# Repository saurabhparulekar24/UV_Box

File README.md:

# UV_Box
Sanitization has become a necessary part of everyone lives, this project provides the design files and firmware for making a PCB of the UV box

The Schematic File provided (.sch) is a Autocad Eagle Schematic File, To Use Autodesk Eagle create an Autodesk account.
NOTE: The Board File and Schematic File names should be same to perform forward and backward annotations in Eagle

Process For Creating PCB
1) Open Schematic and Board file in Eagle, You can make your own changes in the Schematic, this will render the provided board file useless. You will need to create a new board file and Route the PCB (Follow My Blog for PCB designing)
2) Generate CAM Outputs and Forware them to a PCB manufacturing

Although I have also uploaded cam files which can be directly supplied to the PCB manufacturer

The Repository will be updated with new files

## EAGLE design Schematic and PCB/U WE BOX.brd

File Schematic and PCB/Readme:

Eagle ".sch" files and ".brd" files

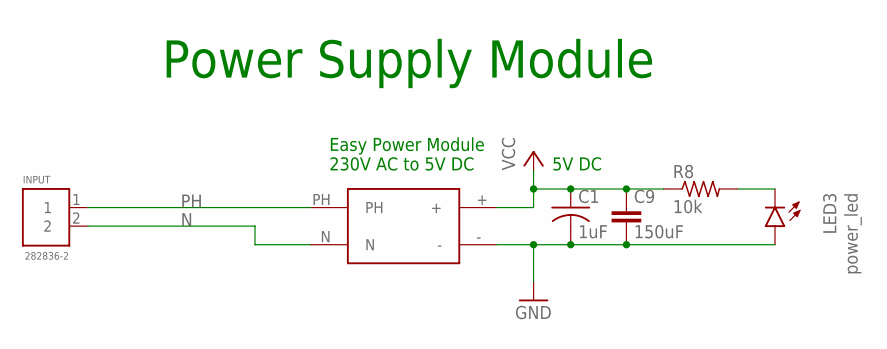
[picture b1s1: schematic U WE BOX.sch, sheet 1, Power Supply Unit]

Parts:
C1: 1uF; C1206K
C9: 150uF; C5B5
INPUT: 282836-2; CONN_282836-2
LED3: power_led; CHIPLED_1206
R8: 10k; M1206
U2: AC/DCCONVERTER; ACDC

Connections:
GND: C1.2, C9.2, LED3.A, U2.-; also elsewhere on the board
N: INPUT.2, U2.N; also elsewhere on the board
unnamed: LED3.C, R8.2
PH: INPUT.1, U2.PH; also elsewhere on the board
VCC: C1.1, C9.1, R8.1, U2.+; also elsewhere on the board

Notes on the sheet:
Easy Power Module 230V AC to 5V DC
5V DC
Power Supply Module

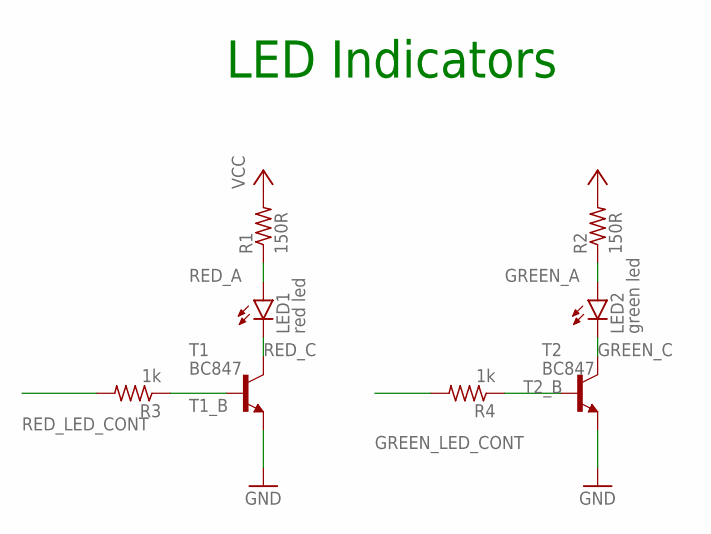
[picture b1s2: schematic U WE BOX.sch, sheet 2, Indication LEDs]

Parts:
LED1: red led; CHIPLED_1206
LED2: green led; CHIPLED_1206
R1, R2: 150R; R1206
R3, R4: 1k; R1206
T1, T2: BC847; SOT23

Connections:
GND: T1.2 (E), T2.2 (E); also elsewhere on the board
GREEN_A: LED2.A, R2.1
GREEN_C: LED2.C, T2.3 (C)
GREEN_LED_CONT: R4.2; also elsewhere on the board
RED_A: LED1.A, R1.1
RED_C: LED1.C, T1.3 (C)
RED_LED_CONT: R3.2; also elsewhere on the board
T1_B: R3.1, T1.1 (B)
T2_B: R4.1, T2.1 (B)
VCC: R1.2, R2.2; also elsewhere on the board

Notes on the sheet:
LED Indicators

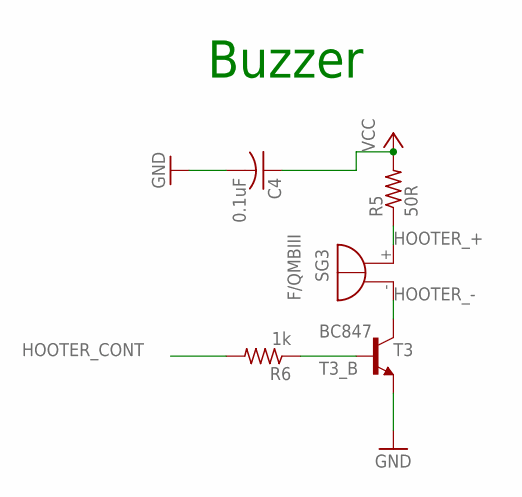
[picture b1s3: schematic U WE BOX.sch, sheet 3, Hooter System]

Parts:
C4: 0.1uF; C1206K
R5: 50R; R1206
R6: 1k; R1206
SG3: F/QMBIII
T3: BC847; SOT23

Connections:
GND: C4.2, T3.2 (E); also elsewhere on the board
HOOTER_+: R5.1, SG3.+ (-)
HOOTER_-: SG3.- (+), T3.3 (C)
HOOTER_CONT: R6.2; also elsewhere on the board
T3_B: R6.1, T3.1 (B)
VCC: C4.1, R5.2; also elsewhere on the board

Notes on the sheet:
Buzzer

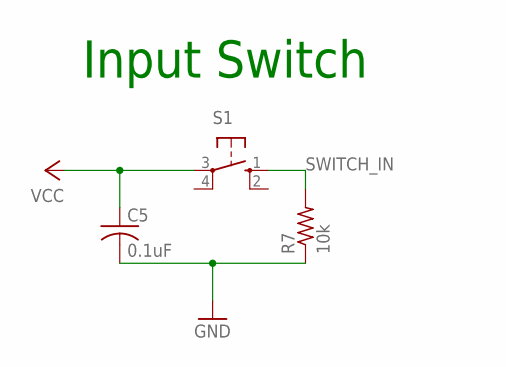
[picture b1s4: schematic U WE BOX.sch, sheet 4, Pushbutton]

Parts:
C5: 0.1uF; C1206K
R7: 10k; R1206
S1: 40-XX; B3F-40XX

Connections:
GND: C5.2, R7.1; also elsewhere on the board
SWITCH_IN: R7.2, S1.1 (S); also elsewhere on the board
VCC: C5.1, S1.3; also elsewhere on the board

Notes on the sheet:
Input Switch

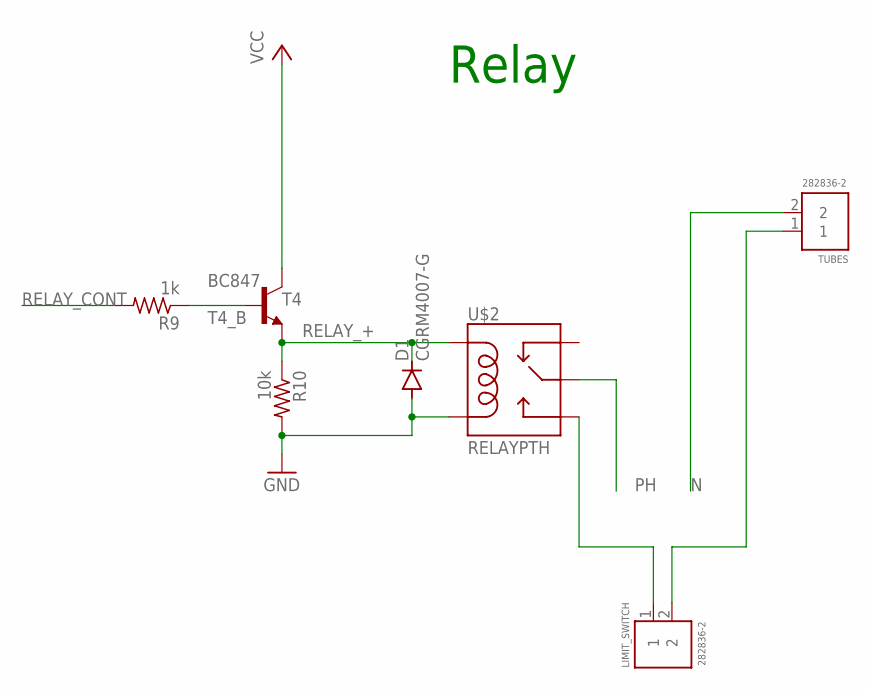
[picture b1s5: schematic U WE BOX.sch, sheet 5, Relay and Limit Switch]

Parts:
D1: CGRM4007-G; SOD-123_MINI-SMA
LIMIT_SWITCH: 282836-2; CONN_282836-2
R9: 1k; R1206
R10: 10k; R1206
T4: BC847; SOT23
TUBES: 282836-2; CONN_282836-2
U$2: RELAYPTH; SRD-05VDC-SL-C

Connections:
GND: D1.A, R10.2, U$2.COIL0; also elsewhere on the board
N: TUBES.2; also elsewhere on the board
PH: U$2.SWCOMMON; also elsewhere on the board
PH_RELAY: LIMIT_SWITCH.1, U$2.SWOPEN
RELAY_+: D1.C, R10.1, T4.2 (E), U$2.COIL1
RELAY_CONT: R9.2; also elsewhere on the board
T4_B: R9.1, T4.1 (B)
TUBE_N: LIMIT_SWITCH.2, TUBES.1
VCC: T4.3 (C); also elsewhere on the board

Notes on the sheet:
Relay

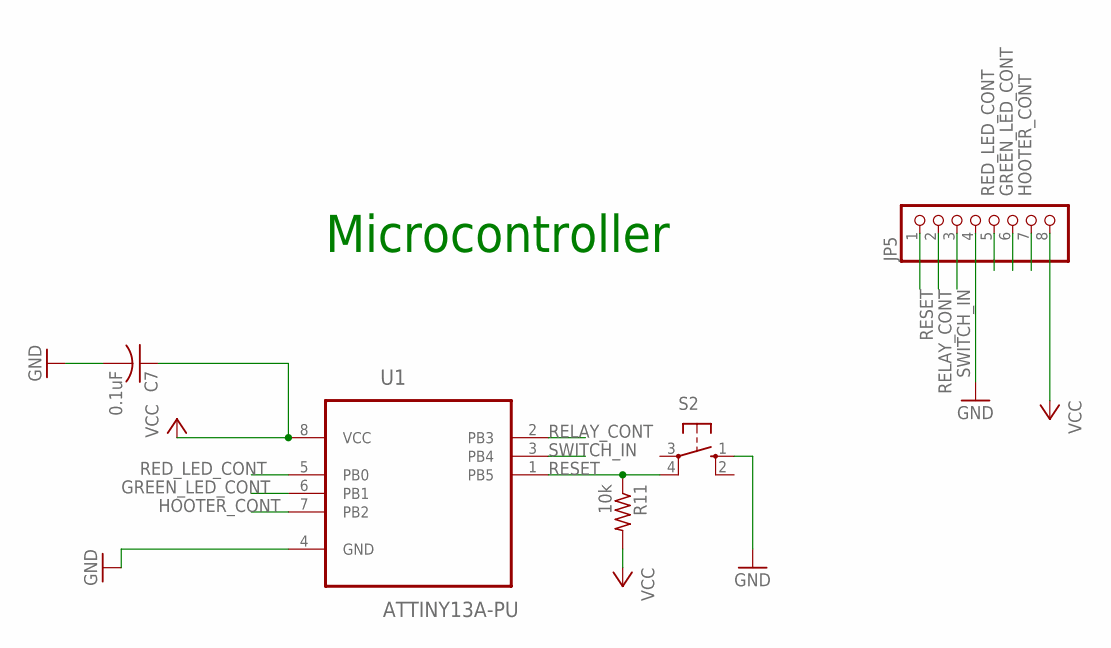
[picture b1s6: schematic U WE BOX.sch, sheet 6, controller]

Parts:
C7: 0.1uF; C1206K
JP5: PINHD-1X8; 1X08
R11: 10k; R1206
S2: 10-XX; B3F-10XX
U1: ATTINY13A-PU; DIP254P762X533-8

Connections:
GND: C7.2, JP5.4, S2.1 (S), U1.4 (GND); also elsewhere on the board
GREEN_LED_CONT: JP5.6, U1.6 (PB1); also elsewhere on the board
HOOTER_CONT: JP5.7, U1.7 (PB2); also elsewhere on the board
RED_LED_CONT: JP5.5, U1.5 (PB0); also elsewhere on the board
RELAY_CONT: JP5.2, U1.2 (PB3); also elsewhere on the board
RESET: JP5.1, R11.1, S2.4 (P1), U1.1 (PB5)
SWITCH_IN: JP5.3, U1.3 (PB4); also elsewhere on the board
VCC: C7.1, JP5.8, R11.2, U1.8 (VCC); also elsewhere on the board

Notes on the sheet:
Microcontroller

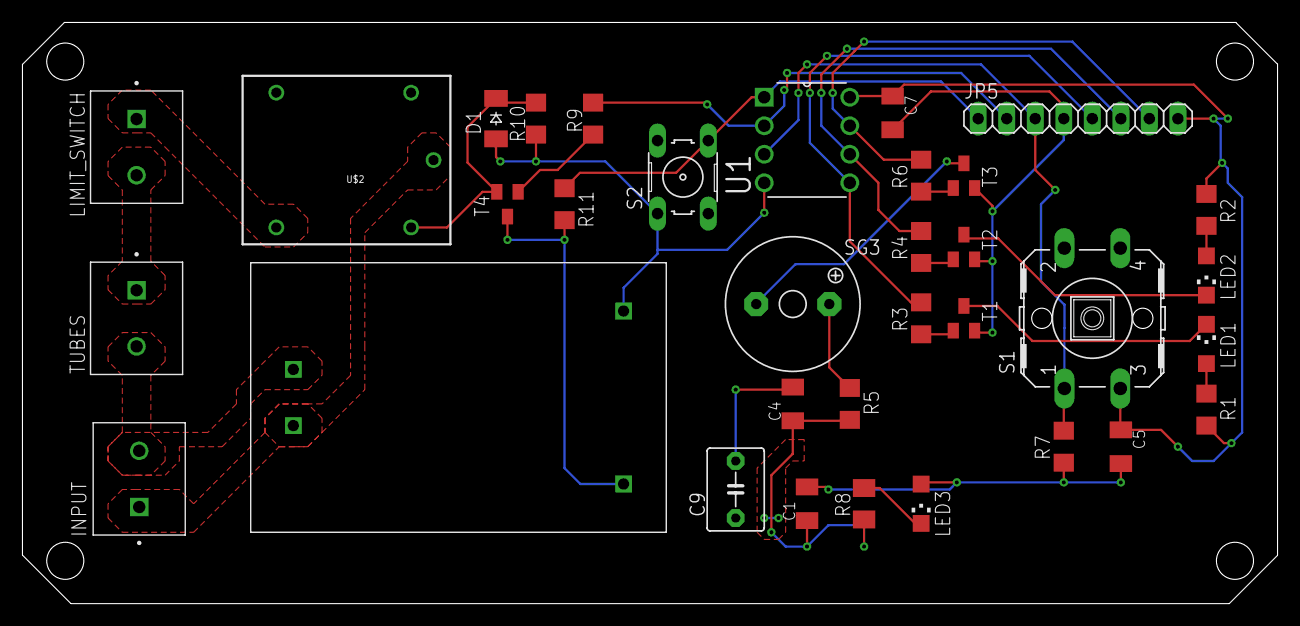
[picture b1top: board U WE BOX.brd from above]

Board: 2 copper layers, 111.7 x 51.7 mm, 34 parts (0 on the bottom side), 24 nets.

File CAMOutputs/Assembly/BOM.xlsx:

Qty | Value | Device | Package | Parts | Description | AVAILABILITY | CENTERLINE_PITCH | COMMENT | DESCRIPTION.1 | EU_ROHS_COMPLIANCE | MF | MP | MPN | NUMBER_OF_POSITIONS | OC_FARNELL | OC_NEWARK | PACKAGE.1 | POPULARITY | PRICE | PURCHASE-URL | SPICEPREFIX | Column1
1 |  | 10-XX | B3F-10XX | S2 | OMRON SWITCH |  |  |  |  |  |  |  | B3F-1000 |  | 176432 | 36M3542 |  | 72
1 |  | 40-XX | B3F-40XX | S1 | OMRON SWITCH |  |  |  |  |  | OMRON COMPONENTS USA |  | B3F-4000 |  | 176434 | 36K3105 |  | 5
1 |  | PINHD-1X8 | 1X08 | JP5 | PIN HEADER |  |  |  |  |  |  |  |  |  |  |  |  | 67
3 | 0.1uF | C-USC1206K | C1206K | C4, C5, C7 | CAPACITOR, American symbol |  |  |  |  |  |  |  |  |  |  |  |  | 2 |  |  | C
1 | 10k | R-US_M1206 | M1206 | R8 | RESISTOR, American symbol |  |  |  |  |  |  |  |  |  |  |  |  | 22 |  |  | R
3 | 10k | R-US_R1206 | R1206 | R7, R10, R11 | RESISTOR, American symbol |  |  |  |  |  |  |  |  |  |  |  |  | 19 |  |  | R
2 | 150R | R-US_R1206 | R1206 | R1, R2 | RESISTOR, American symbol |  |  |  |  |  |  |  |  |  |  |  |  | 19 |  |  | R
1 | 150uF | C5/5 | C5B5 | C9 | CAPACITOR |  |  |  |  |  |  |  |  |  |  |  |  | 1
4 | 1k | R-US_R1206 | R1206 | R3, R4, R6, R9 | RESISTOR, American symbol |  |  |  |  |  |  |  |  |  |  |  |  | 19 |  |  | R
1 | 1uF | C-USC1206K | C1206K | C1 | CAPACITOR, American symbol |  |  |  |  |  |  |  |  |  |  |  |  | 2 |  |  | C
3 | 282836-2 | 282836-2 | CONN_282836-2 | INPUT, LIMIT_SWITCH, TUBES | TERM BLOCK 2POS SIDE ENTRY 5MM Check prices | Good | 5 mm[.197 in] | 282836-2 | Connector, Terminal Block | Wire Receptacle | 2 Pos. | 16-30 AWG | 0.197 in. CL | Sid | Compliant with Exemptions | TE Connectivity | 282836-2 |  | 2
1 | 50R | R-US_R1206 | R1206 | R5 | RESISTOR, American symbol |  |  |  |  |  |  |  |  |  |  |  |  | 19 |  |  | R
1 | AC/DCCONVERTER | AC/DCCONVERTER | ACDC | U2
1 | ATTINY13A-PU | ATTINY13A-PU | DIP254P762X533-8 | U1 | 8-bit Microcontroller with 1K Bytes In-System Programmable Flash Check prices | Good |  |  | AVR AVRÂ® ATtiny Microcontroller IC 8-Bit 20MHz 1KB (512 x 16) FLASH 8-PDIP |  | Microchip | ATTINY13A-PU |  |  |  |  | PDIP-8 Microchip |  | None | https://pricing.snapeda.com/search/part/ATTINY13A-PU/?ref=eda
4 | BC847 | BC847 | SOT23 | T1, T2, T3, T4 | NPN TRANSISTOR |  |  |  |  |  |  |  |  |  |  |  |  | 5
1 | CGRM4007-G | CGRM4007-G | SOD-123_MINI-SMA | D1 | Molded plasitc,JEDEC SOD-123/Mini SMA |  |  |  |  |  |  |  |  |  |  |  |  | 0
1 | F/QMBIII | F/QMBIII | F/QMBIII | SG3 | BUZZER Source: Buerklin |  |  |  |  |  |  |  |  |  | unknown | unknown |  | 1
1 | RELAYPTH | RELAYPTH | SRD-05VDC-SL-C | U$2 | SPDT relay (COM-00101)
1 | green led | LEDCHIPLED_1206 | CHIPLED_1206 | LED2 | LED |  |  |  |  |  |  |  |  |  |  |  |  | 28
1 | power_led | LEDCHIPLED_1206 | CHIPLED_1206 | LED3 | LED |  |  |  |  |  |  |  |  |  |  |  |  | 28
1 | red led | LEDCHIPLED_1206 | CHIPLED_1206 | LED1 | LED |  |  |  |  |  |  |  |  |  |  |  |  | 28

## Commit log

2021-01-26 ./CAMoutputs
